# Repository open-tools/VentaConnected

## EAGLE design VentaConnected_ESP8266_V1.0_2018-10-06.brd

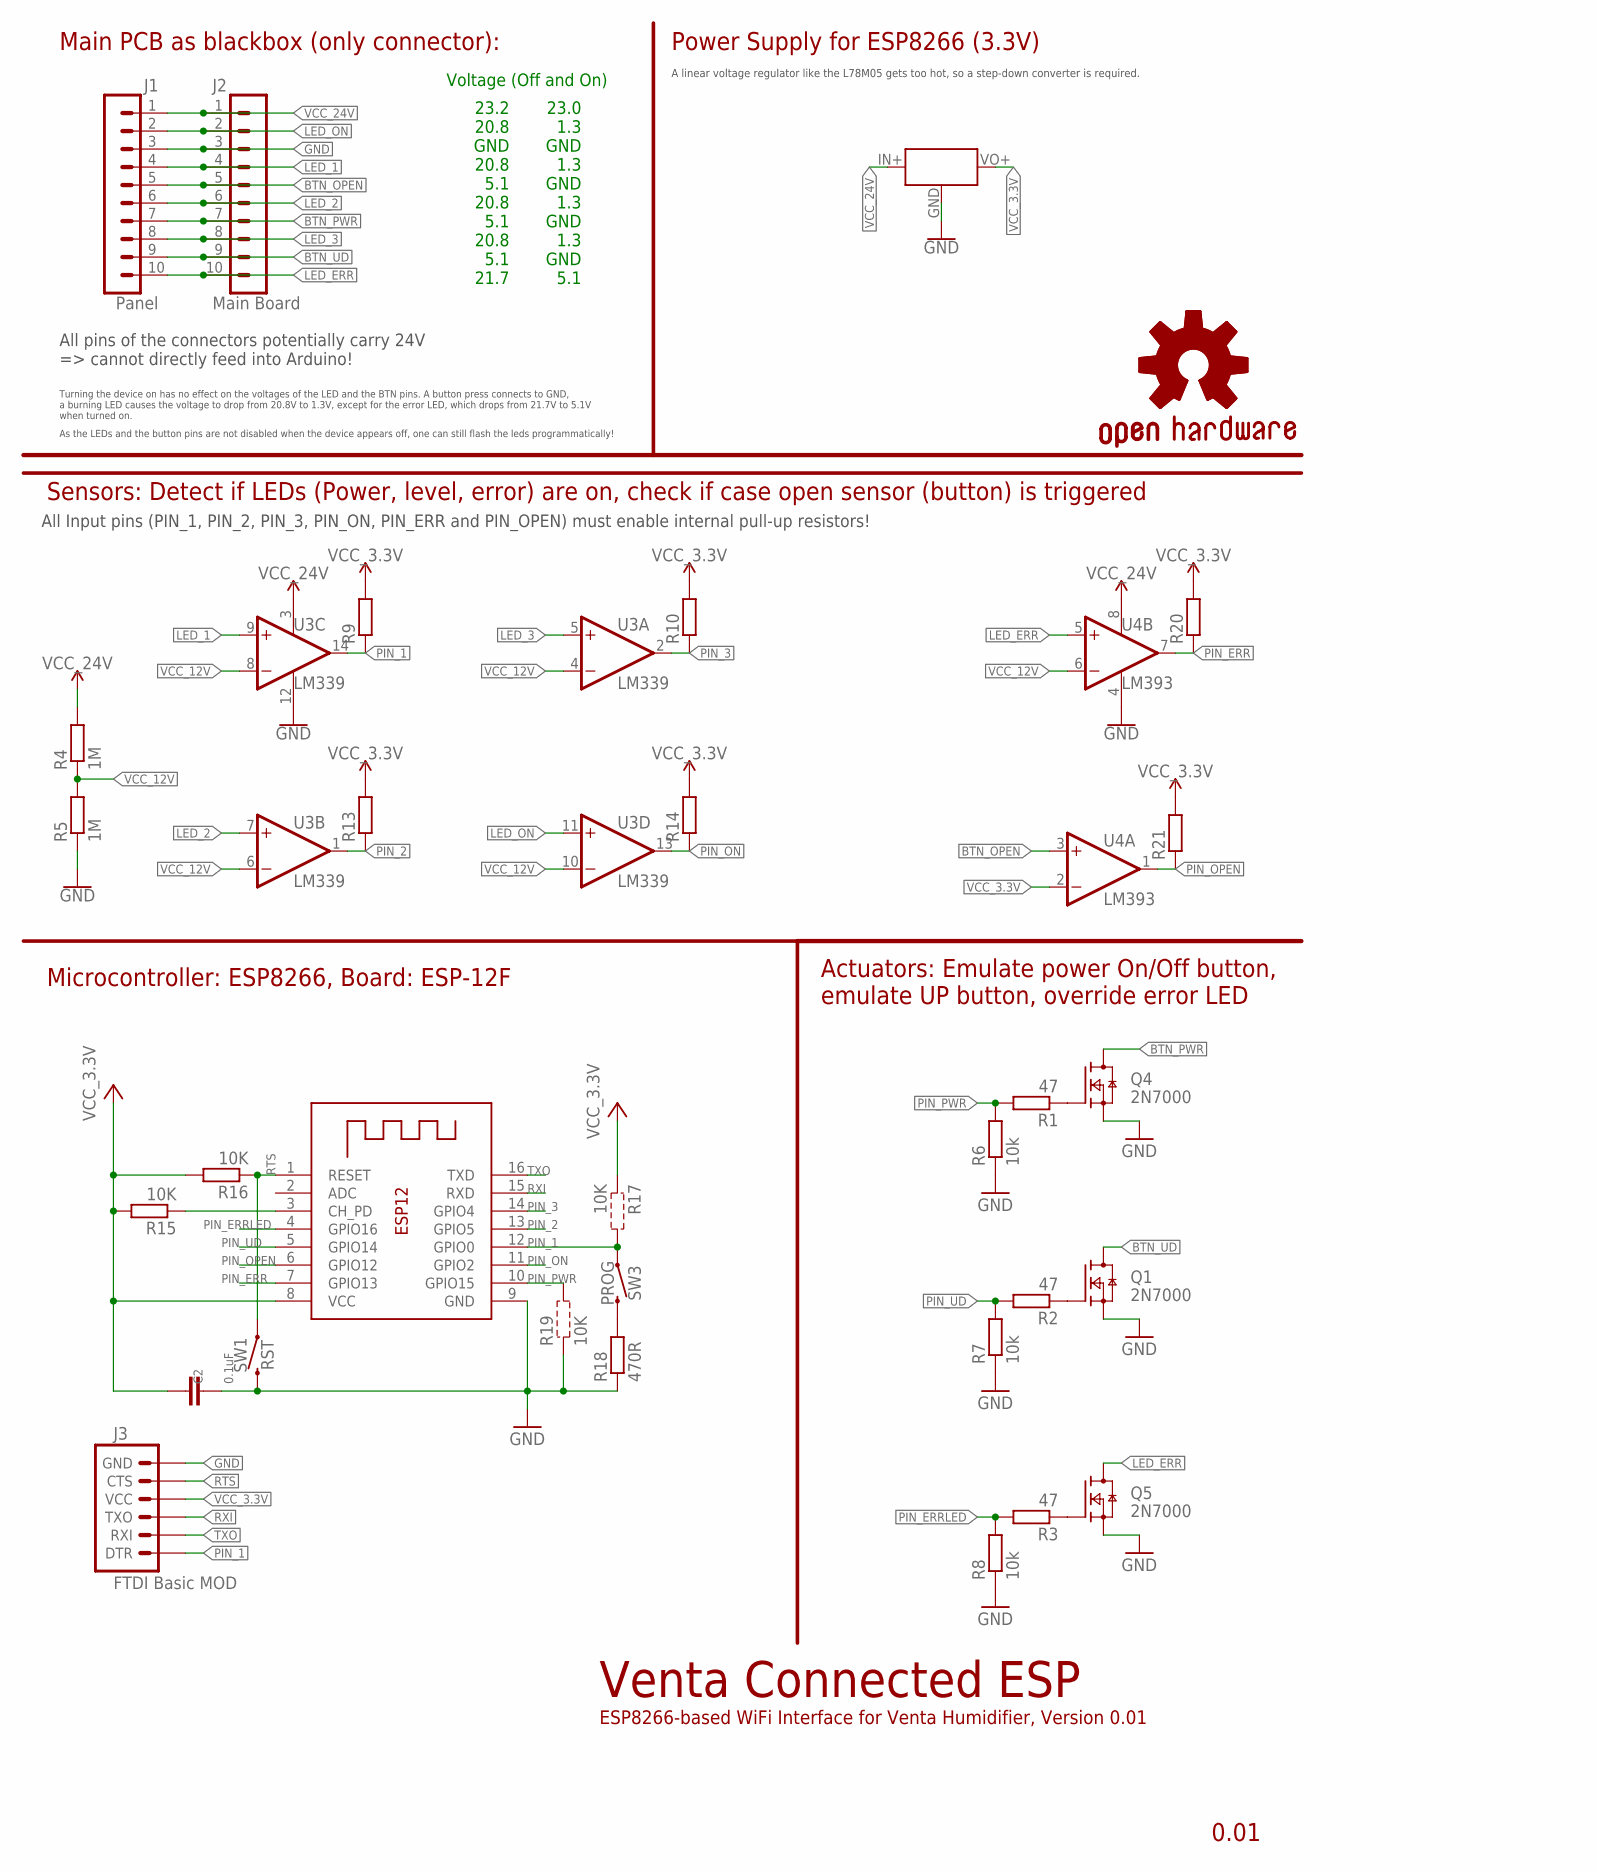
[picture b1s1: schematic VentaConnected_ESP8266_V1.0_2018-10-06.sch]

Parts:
C2: 0.1uF; C0805
GOLD_ORB_SM1: OSHWLOGO_GOLD_ORB_SM; OSHW2
J1: Panel; 2X5-SHROUDED
J2: Main Board; 2X5
J3: FTDI Basic MOD; 1X06
Q1, Q4, Q5: 2N7000; SOT23
R1, R2, R3: 47; R0805
R4, R5: 1M; R0805
R6, R7, R8: 10k; R0805
R9, R10, R13, R14, R20, R21: R-EU_R0805; R0805
R15, R16: 10K; R0805
R18: 470R; R0805
SW1: RST; TACTILE_SWITCH_SMD_6.0X3.5MM
SW3: PROG; TACTILE_SWITCH_SMD_6.0X3.5MM
U2: 3.3V_BUCK_CONVERTER; MINI_BUCK_CONVERTER_UPDOWN
U3: LM339; SO14
U4: LM393; SO08
X2: ESP-12e; ESP-12

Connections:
BTN_OPEN: J1.5, J2.5, U4.3 (+IN)
BTN_PWR: J1.7, J2.7, Q4.3 (D)
BTN_UD: J1.9, J2.9, Q1.3 (D)
CH_PD: R15.1, X2.3 (CH_PD)
GND: C2.1, J1.3, J2.3, J3.6 (GND), Q1.2 (S), Q4.2 (S), Q5.2 (S), R5.1, R6.1, R7.1, R8.1, R18.1, SW1.2, U2.GND, U3.12 (V-), U4.4 (V-), X2.9 (GND)
LED_1: J1.4, J2.4, U3.9 (+IN)
LED_2: J1.6, J2.6, U3.7 (+IN)
LED_3: J1.8, J2.8, U3.5 (+IN)
LED_ERR: J1.10, J2.10, Q5.3 (D), U4.5 (+IN)
LED_ON: J1.2, J2.2, U3.11 (+IN)
unnamed: Q4.1 (G), R1.1
unnamed: R18.2, SW3.2
unnamed: Q5.1 (G), R3.1
unnamed: Q1.1 (G), R2.1
PIN_1: J3.1 (DTR), R9.1, SW3.1, U3.14 (OUT), X2.12 (GPIO0)
PIN_2: R13.1, U3.1 (OUT), X2.13 (GPIO5)
PIN_3: R10.1, U3.2 (OUT), X2.14 (GPIO4)
PIN_ERR: R20.1, U4.7 (OUT), X2.7 (GPIO13)
PIN_ERRLED: R3.2, R8.2, X2.4 (GPIO16)
PIN_ON: R14.1, U3.13 (OUT), X2.11 (GPIO2)
PIN_OPEN: R21.1, U4.1 (OUT), X2.6 (GPIO12)
PIN_PWR: R1.2, R6.2, X2.10 (GPIO15)
PIN_UD: R2.2, R7.2, X2.5 (GPIO14)
RTS: J3.5 (CTS), R16.1, SW1.1, X2.1 (RESET)
RXI: J3.3 (TXO), X2.15 (RXD)
TXO: J3.2 (RXI), X2.16 (TXD)
VCC_3.3V: C2.2, J3.4 (VCC), R9.2, R10.2, R13.2, R14.2, R15.2, R16.2, R20.2, R21.2, U2.VO+ (VOUT), U4.2 (-IN), X2.8 (VCC)
VCC_12V: R4.1, R5.2, U3.4 (-IN), U3.6 (-IN), U3.8 (-IN), U3.10 (-IN), U4.6 (-IN)
VCC_24V: J1.1, J2.1, R4.2, U2.IN+ (VIN), U3.3 (V+), U4.8 (V+)

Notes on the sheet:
Power Supply for ESP8266 (3.3V)
ESP8266-based WiFi Interface for Venta Humidifier, Version 0.01
Venta Connected ESP
Actuators: Emulate power On/Off button, emulate UP button, override error LED
Sensors: Detect if LEDs (Power, level, error) are on, check if case open sensor (button) is triggered
Microcontroller: ESP8266, Board: ESP-12F
Main PCB as blackbox (only connector):
All pins of the connectors potentially carry 24V => cannot directly feed into Arduino!
A linear voltage regulator like the L78M05 gets too hot, so a step-down converter is required.
Voltage (Off and On)
23.2 20.8 GND 20.8 5.1 20.8 5.1 20.8 5.1 21.7
23.0 1.3 GND 1.3 GND 1.3 GND 1.3 GND 5.1
Turning the device on has no effect on the voltages of the LED and the BTN pins. A button press connects to GND, a burning LED causes the voltage to drop from 20.8V to 1.3V, except for the error LED, which drops from 21.7V to 5.1V when turned on.
As the LEDs and the button pins are not disabled when the device appears off, one can still flash the leds programmatically!
All Input pins (PIN_1, PIN_2, PIN_3, PIN_ON, PIN_ERR and PIN_OPEN) must enable internal pull-up resistors!

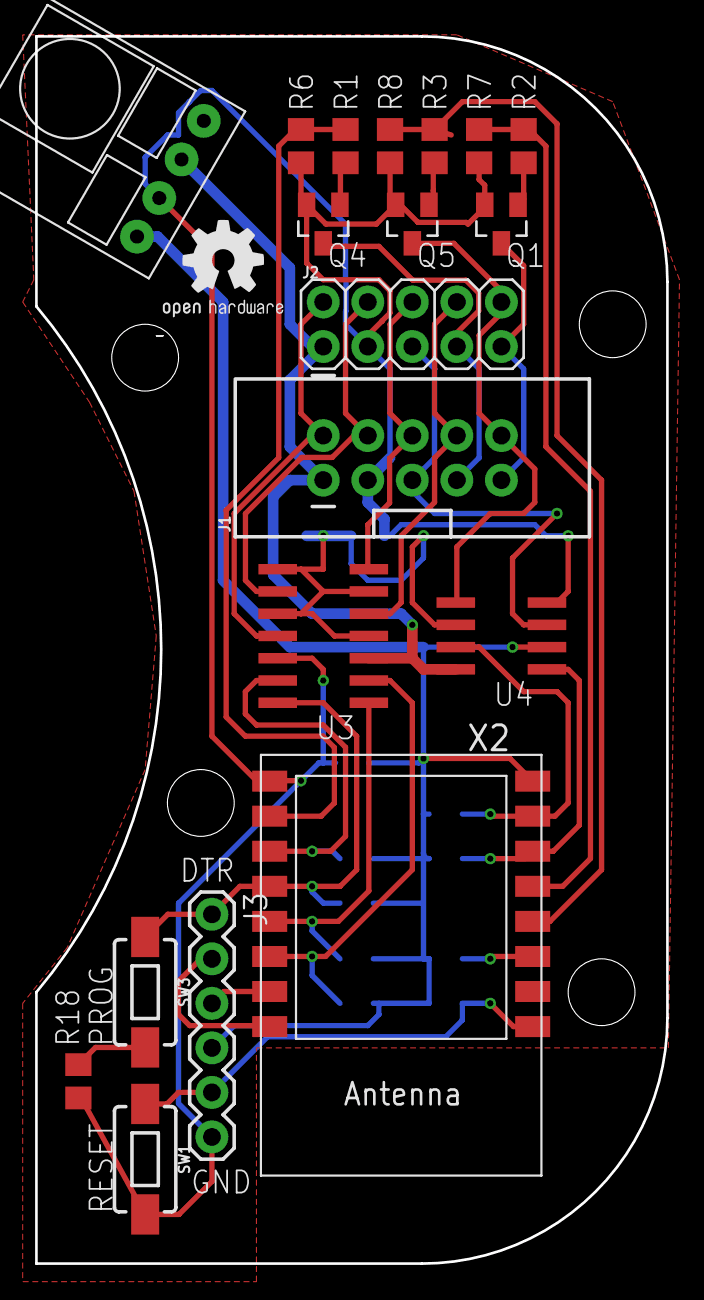
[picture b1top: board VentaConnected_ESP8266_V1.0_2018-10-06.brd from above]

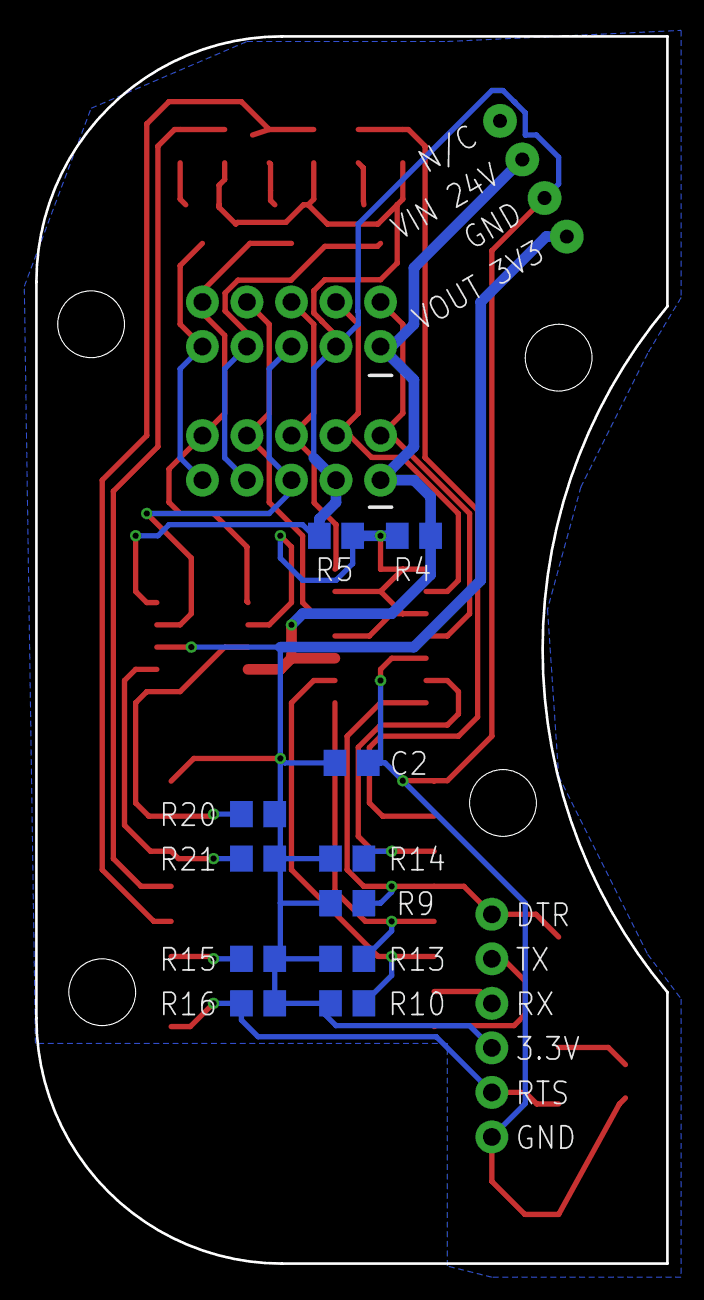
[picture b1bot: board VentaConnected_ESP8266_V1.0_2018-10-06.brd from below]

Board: 2 copper layers, 36.0 x 70.0 mm, 31 parts (11 on the bottom side), 29 nets.

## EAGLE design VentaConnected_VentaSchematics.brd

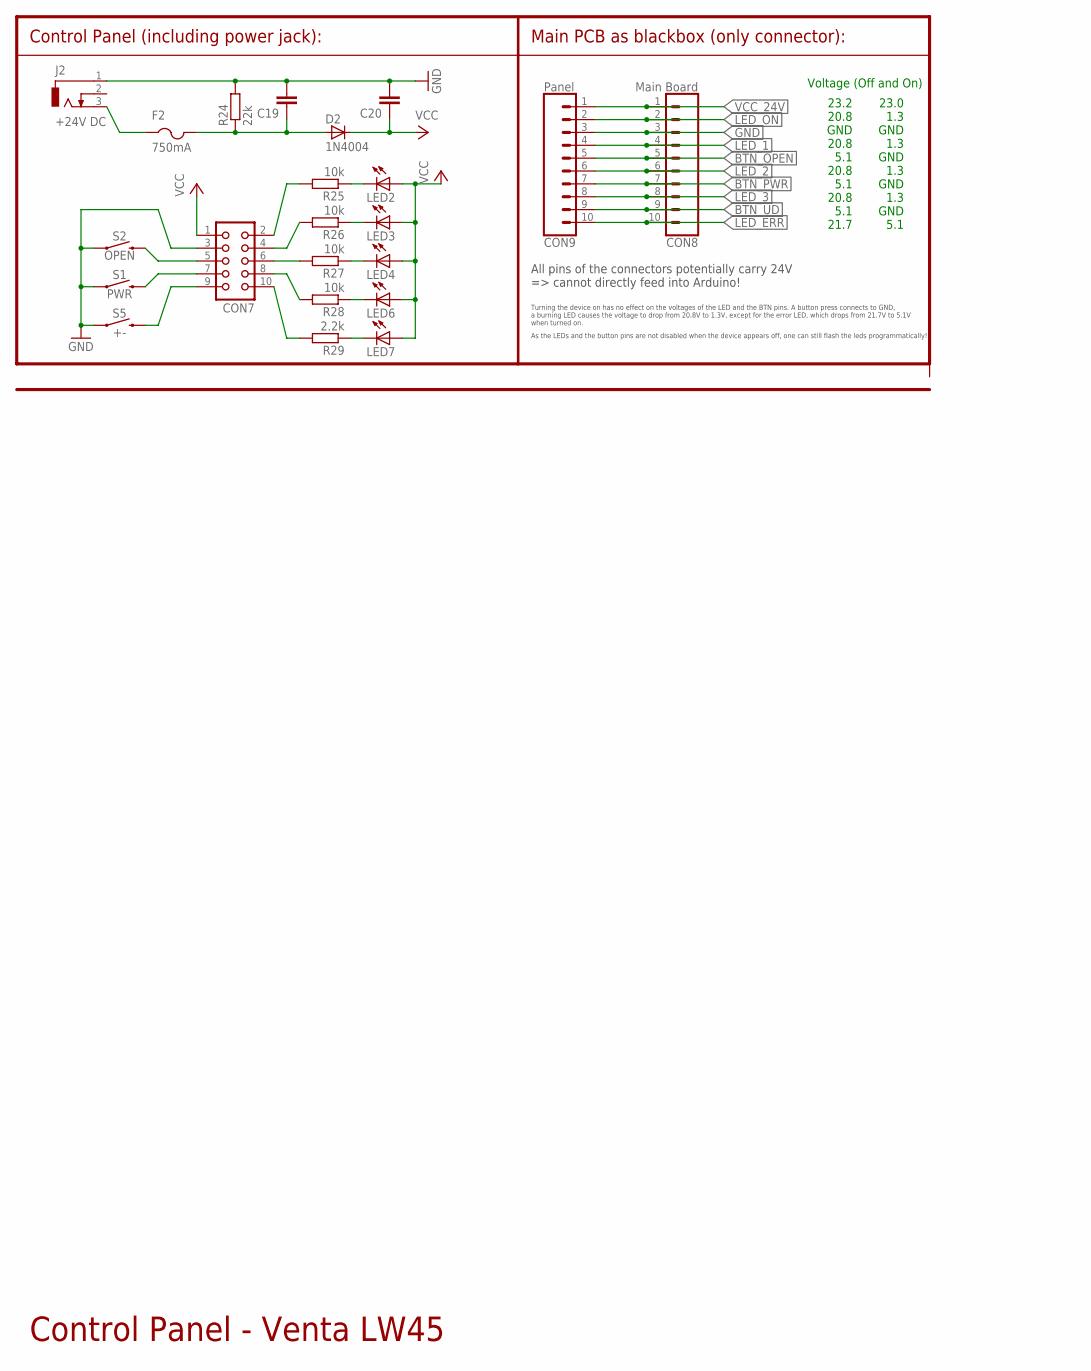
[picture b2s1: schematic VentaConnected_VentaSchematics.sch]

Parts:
C19, C20: C-EUC0805K; C0805K
CON7: CON10
CON8: Main Board; 1X10_LOCK_LONGPADS
CON9: Panel; 1X10_LOCK_LONGPADS
D2: 1N4004; MELF-MLL41
F2: 750mA; 1812
J2: +24V DC; DCJ0202
LED2, LED3, LED4, LED6, LED7: LEDCHIPLED_0805; CHIPLED_0805
R24: 22k; R0805
R25, R26, R27, R28: 10k; R0805
R29: 2.2k; R0805
S1: PWR; TACTILE_SWITCH_PTH_6.0MM
S2: OPEN; TACTILE_SWITCH_PTH_6.0MM
S5: +-; TACTILE_SWITCH_PTH_6.0MM

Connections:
BTN_OPEN: CON7.5, CON8.5, CON9.5, S2.3 (2)
BTN_PWR: CON7.7, CON8.7, CON9.7, S1.3 (2)
BTN_UD: CON7.9, CON8.9, CON9.9, S5.3 (2)
GND: C19.2, C20.2, CON7.3, CON8.3, CON9.3, J2.1, R24.2, S1.1, S2.1, S5.1
LED_1: CON7.4, CON8.4, CON9.4, R26.2
LED_2: CON7.6, CON8.6, CON9.6, R27.2
LED_3: CON7.8, CON8.8, CON9.8, R28.2
LED_ERR: CON7.10, CON8.10, CON9.10, R29.2
LED_ON: CON7.2, CON8.2, CON9.2, R25.2
unnamed: F2.1, J2.3
unnamed: C19.1, D2.2 (A), F2.2, R24.1
unnamed: LED2.C, R25.1
unnamed: LED7.C, R29.1
unnamed: LED3.C, R26.1
unnamed: LED4.C, R27.1
unnamed: LED6.C, R28.1
VCC: C20.1, D2.1 (C), LED2.A, LED3.A, LED4.A, LED6.A, LED7.A
VCC_24V: CON7.1, CON8.1, CON9.1

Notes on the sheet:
Control Panel - Venta LW45
Control Panel (including power jack):
Main PCB as blackbox (only connector):
All pins of the connectors potentially carry 24V => cannot directly feed into Arduino!
Voltage (Off and On)
23.2 20.8 GND 20.8 5.1 20.8 5.1 20.8 5.1 21.7
23.0 1.3 GND 1.3 GND 1.3 GND 1.3 GND 5.1
Turning the device on has no effect on the voltages of the LED and the BTN pins. A button press connects to GND, a burning LED causes the voltage to drop from 20.8V to 1.3V, except for the error LED, which drops from 21.7V to 5.1V when turned on.
As the LEDs and the button pins are not disabled when the device appears off, one can still flash the leds programmatically!

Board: 2 copper layers, 22 parts (0 on the bottom side), 18 nets, no tracks yet.

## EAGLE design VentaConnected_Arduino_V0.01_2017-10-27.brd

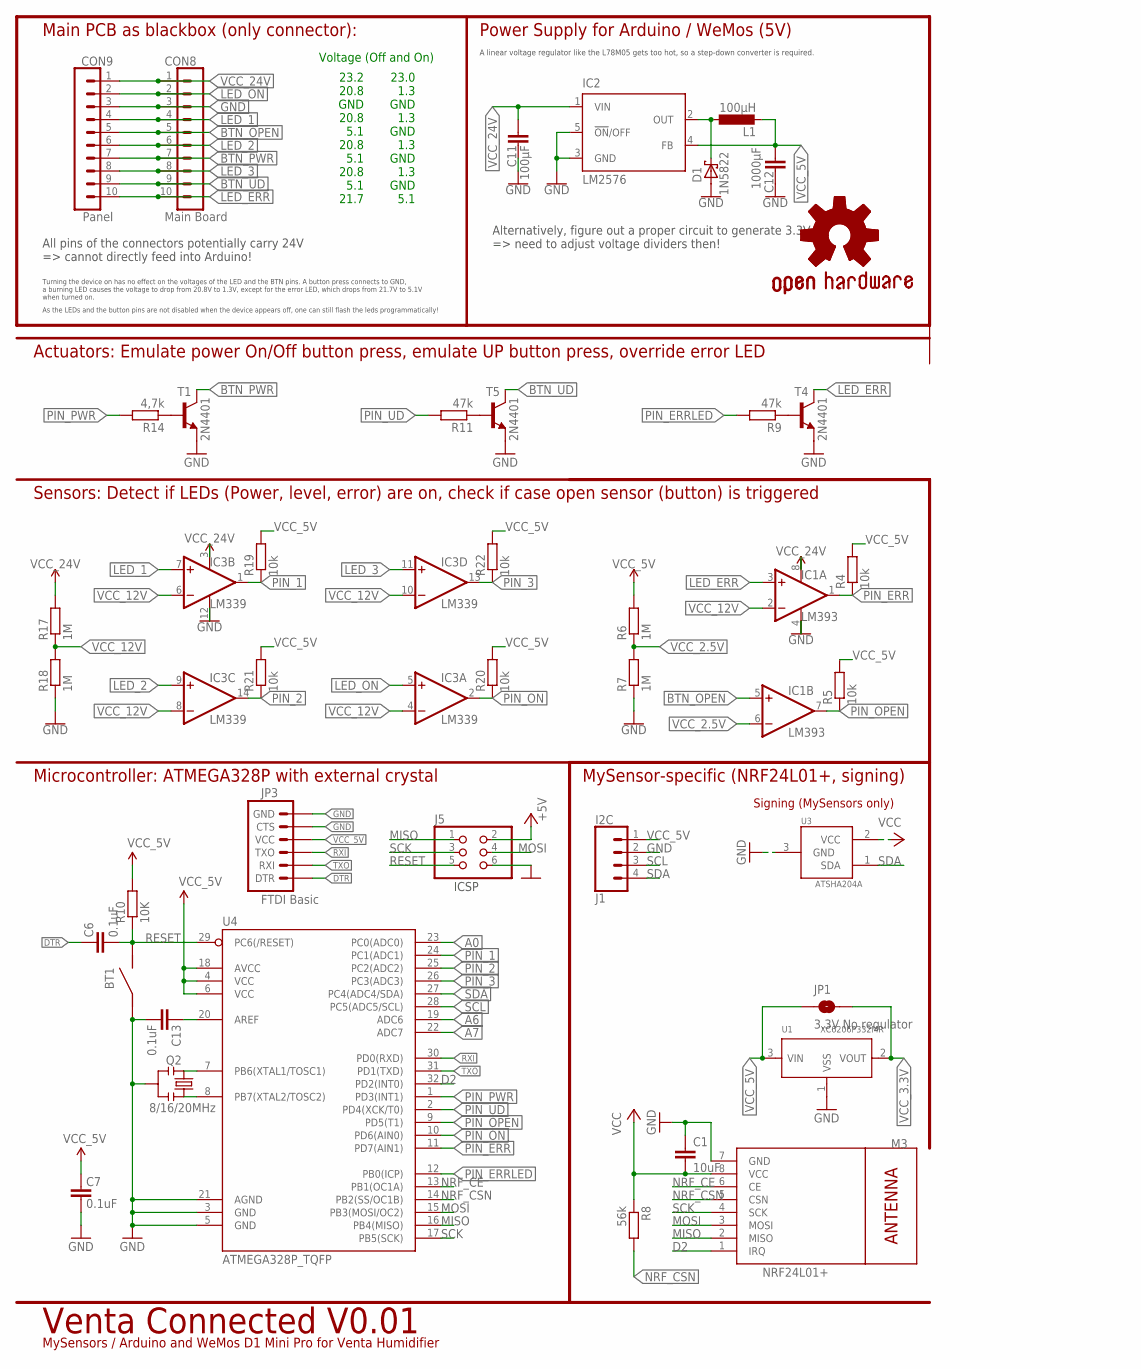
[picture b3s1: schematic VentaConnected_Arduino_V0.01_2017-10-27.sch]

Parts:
BT1: SWITCHPROMINI_RESET; SWITCH_SMD_PROMINI_RESET
C1: 10uF; C0805
C6, C7, C13: 0.1uF; 0603-CAP
C11: 100µF; C0805
C12: 1000µF; C0805
CON8: Main Board; 2X5
CON9: Panel; 2X5-SHROUDED
D1: 1N5822; SMB
GOLD_ORB_SM1: OSHWLOGO_GOLD_ORB_SM; OSHW2
IC1: LM393; SO08
IC2: LM2576; TO263-5
IC3: LM339; SO14
J1: I2C; 1X04
J5: PINHD-2X3; 2X03
JP1: 3.3V No regulator; SMT-JUMPER_2_NO_SILK
JP3: FTDI Basic; 1X06
L1: 100µH; POWER-CHOKE_WE-TPC
M3: NRF24L01+; WIRELESS-NRF24L01-SMD
Q2: 8/16/20MHz; RESONATOR-SMD-1:1
R4, R5, R19, R20, R21, R22: 10k; R0805
R6, R7, R17, R18: 1M; R0805
R8: 56k; R0805
R9, R11: 47k; R0805
R10: 10K; R0805
R14: 4,7k; R0805
T1, T4, T5: 2N4401; SOT23-BEC
U1: XC6206P332MR; SOT-23
U3: ATSHA204A; SOT23-3
U4: ATMEGA328P_TQFP; TQFP32-08

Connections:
A0: U4.23 (PC0(ADC0))
A6: U4.19 (ADC6)
A7: U4.22 (ADC7)
AREF: C13.2, U4.20 (AREF)
BTN_OPEN: CON8.5, CON9.5, IC1.5 (+IN)
BTN_PWR: CON8.7, CON9.7, T1.C
BTN_UD: CON8.9, CON9.9, T5.C
D2: M3.1 (IRQ), U4.32 (PD2(INT0))
DTR: C6.2, JP3.1 (DTR)
GND: BT1.IN, C7.1, C11.2, C12.2, C13.1, CON8.3, CON9.3, D1.A, IC1.4 (V-), IC2.3 (GND), IC2.5 (!ON!/OFF), IC3.12 (V-), J1.2, J5.6, JP3.5 (CTS), JP3.6 (GND), Q2.2, R7.1, R18.1, T1.E, T4.E, T5.E, U4.3 (GND), U4.5 (GND), U4.21 (AGND)
GND_ARD: C1.1, M3.7 (GND), U3.3 (GND)
LED_1: CON8.4, CON9.4, IC3.7 (+IN)
LED_2: CON8.6, CON9.6, IC3.9 (+IN)
LED_3: CON8.8, CON9.8, IC3.11 (+IN)
LED_ERR: CON8.10, CON9.10, IC1.3 (+IN), T4.C
LED_ON: CON8.2, CON9.2, IC3.5 (+IN)
MISO: J5.1, M3.2 (MISO), U4.16 (PB4(MISO))
MOSI: J5.4, M3.3 (MOSI), U4.15 (PB3(MOSI/OC2))
unnamed: D1.C, IC2.2 (OUT), L1.1
unnamed: R14.1, T1.B
unnamed: R9.1, T4.B
unnamed: R11.1, T5.B
unnamed: Q2.3, U4.8 (PB7(XTAL2/TOSC2))
unnamed: Q2.1, U4.7 (PB6(XTAL1/TOSC1))
NRF_CE: M3.6 (CE), U4.13 (PB1(OC1A))
NRF_CSN: M3.5 (CSN), R8.2, U4.14 (PB2(SS/OC1B))
PIN_1: IC3.1 (OUT), R19.1, U4.24 (PC1(ADC1))
PIN_2: IC3.14 (OUT), R21.1, U4.25 (PC2(ADC2))
PIN_3: IC3.13 (OUT), R22.1, U4.26 (PC3(ADC3))
PIN_ERR: IC1.1 (OUT), R4.1, U4.11 (PD7(AIN1))
PIN_ERRLED: R9.2, U4.12 (PB0(ICP))
PIN_ON: IC3.2 (OUT), R20.1, U4.10 (PD6(AIN0))
PIN_OPEN: IC1.7 (OUT), R5.1, U4.9 (PD5(T1))
PIN_PWR: R14.2, U4.1 (PD3(INT1))
PIN_UD: R11.2, U4.2 (PD4(XCK/T0))
RESET: BT1.OUT, C6.1, J5.5, R10.1, U4.29 (PC6(/RESET))
RXI: JP3.3 (TXO), U4.30 (PD0(RXD))
SCK: J5.3, M3.4 (SCK), U4.17 (PB5(SCK))
SCL: J1.3, U4.28 (PC5(ADC5/SCL))
SDA: J1.4, U3.1 (SDA), U4.27 (PC4(ADC4/SDA))
TXO: JP3.2 (RXI), U4.31 (PD1(TXD))
VCC_2.5V: IC1.6 (-IN), R6.1, R7.2
VCC_3.3V: C1.2, JP1.2, M3.8 (VCC), R8.1, U1.2 (VOUT)
VCC_5V: C7.2, C12.1, IC2.4 (FB), J1.1, J5.2, JP1.1, JP3.4 (VCC), L1.2, R4.2, R5.2, R6.2, R10.2, R19.2, R20.2, R21.2, R22.2, U1.3 (VIN), U3.2 (VCC), U4.4 (VCC), U4.6 (VCC), U4.18 (AVCC)
VCC_12V: IC1.2 (-IN), IC3.4 (-IN), IC3.6 (-IN), IC3.8 (-IN), IC3.10 (-IN), R17.1, R18.2
VCC_24V: C11.1, CON8.1, CON9.1, IC1.8 (V+), IC2.1 (VIN), IC3.3 (V+), R17.2
VSS: U1.1 (VSS)

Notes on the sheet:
Signing (MySensors only)
MySensor-specific (NRF24L01+, signing)
Power Supply for Arduino / WeMos (5V)
MySensors / Arduino and WeMos D1 Mini Pro for Venta Humidifier
Venta Connected V0.01
Actuators: Emulate power On/Off button press, emulate UP button press, override error LED
Sensors: Detect if LEDs (Power, level, error) are on, check if case open sensor (button) is triggered
Microcontroller: ATMEGA328P with external crystal
Alternatively, figure out a proper circuit to generate 3.3V => need to adjust voltage dividers then!
Main PCB as blackbox (only connector):
All pins of the connectors potentially carry 24V => cannot directly feed into Arduino!
A linear voltage regulator like the L78M05 gets too hot, so a step-down converter is required.
Voltage (Off and On)
23.2 20.8 GND 20.8 5.1 20.8 5.1 20.8 5.1 21.7
23.0 1.3 GND 1.3 GND 1.3 GND 1.3 GND 5.1
Turning the device on has no effect on the voltages of the LED and the BTN pins. A button press connects to GND, a burning LED causes the voltage to drop from 20.8V to 1.3V, except for the error LED, which drops from 21.7V to 5.1V when turned on.
As the LEDs and the button pins are not disabled when the device appears off, one can still flash the leds programmatically!
ICSP

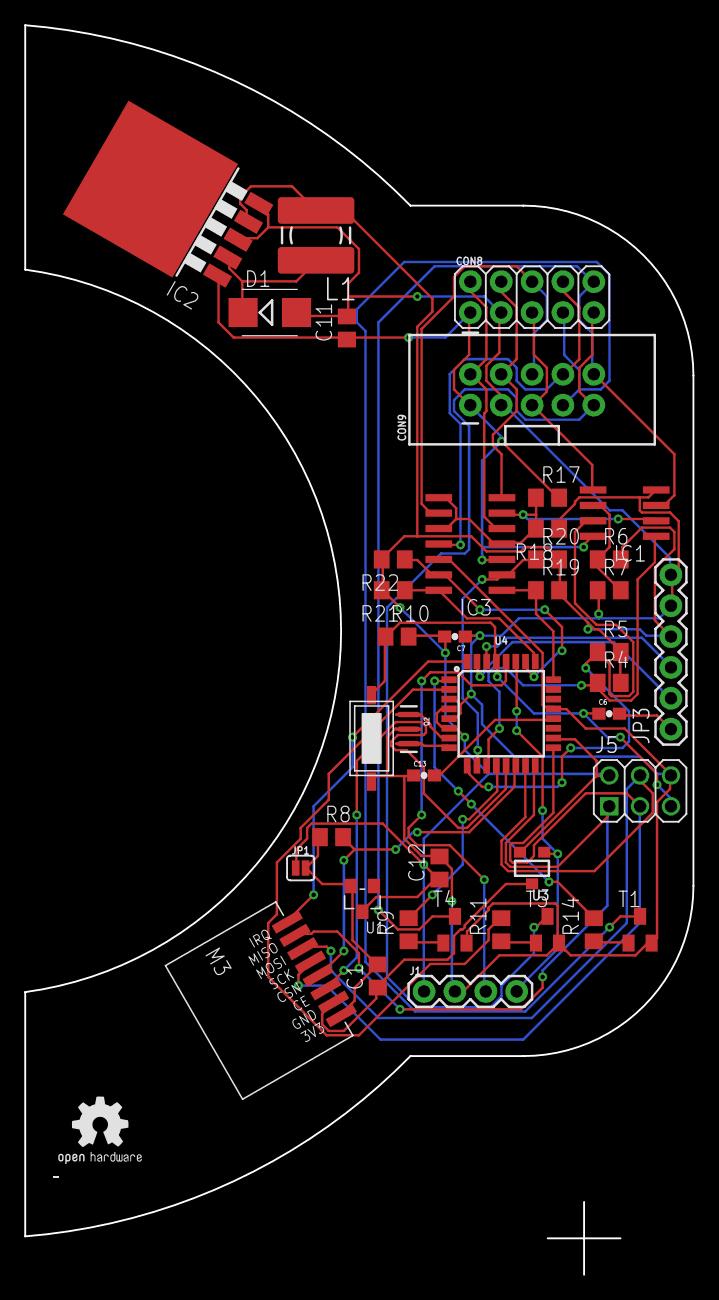
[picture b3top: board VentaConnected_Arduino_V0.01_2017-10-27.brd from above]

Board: 2 copper layers, 55.0 x 102.8 mm, 42 parts (0 on the bottom side), 43 nets.

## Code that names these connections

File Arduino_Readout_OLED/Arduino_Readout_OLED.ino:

/*********************************************************************
This is an example for our Monochrome OLEDs based on SSD1306 drivers

  Pick one up today in the adafruit shop!
  ------> http://www.adafruit.com/category/63_98

This example is for a 128x64 size display using I2C to communicate
3 pins are required to interface (2 I2C and one reset)

Adafruit invests time and resources providing this open source code, 
please support Adafruit and open-source hardware by purchasing 
products from Adafruit!

Written by Limor Fried/Ladyada  for Adafruit Industries.  
BSD license, check license.txt for more information
All text above, and the splash screen must be included in any redistribution
*********************************************************************/
//#define SSD1306_128_64

//#include <SPI.h>
//#include <Wire.h>
//#include <Adafruit_GFX.h>
//#include <Adafruit_SSD1306.h>

//#define OLED_RESET 4
//Adafruit_SSD1306 display(OLED_RESET);
//#if (SSD1306_LCDHEIGHT != 64)
//# error(F("Height incorrect, please fix Adafruit_SSD1306.h!"));
//#endif

#include <SSD1306Ascii.h>
#include <SSD1306AsciiAvrI2c.h>
// 0X3C+SA0 - 0x3C or 0x3D
#define I2C_ADDRESS 0x3C
SSD1306AsciiAvrI2c oled;

#define PIN_PWR  3
#define PIN_UD   4
#define PIN_OPEN 5
#define LED_ON   6
#define LED_1    A1
#define LED_2    A2
#define LED_3    A3
#define LED_ERR  7
#define PIN_ERR  8


void setup()   {                
  Serial.begin(9600);

  // by default, we'll generate the high voltage from the 3.3v line internally! (neat!)
//  display.begin(SSD1306_SWITCHCAPVCC, 0x3D);  // initialize with the I2C addr 0x3D (for the 128x64)
//  display.begin(SSD1306_SWITCHCAPVCC, 0x3C);  // initialize with the I2C addr 0x3D (for the 128x64)
  // init done
//  display.clearDisplay();
  oled.begin(&Adafruit128x64, I2C_ADDRESS);
  oled.setFont(Adafruit5x7);

  // Set up pins:
  // Button & LED Actions (output):
  //   - PIN_PWR  D3 ... Power button press
  //   - PIN_UD   D4 ... Up/Down button press
  //   - PIN_ERR  D8 ... Control Error LED
  // Button detection (input, pullup!):
  //   - PIN_OPEN D5 ... Case open Button => causes Error
  // LED detection (input, NO pullup, already connected to +VCC via LED+resistor):
  //   - LED_ON   D6 ... Power LED 
  //   - LED_ERR  D7 ... Error LED
  //   - LED_1    A1 ... Level 1 LED
  //   - LED_2    A2 ... Level 2 LED
  //   - LED_3    A3 ... Level 3 LED

  pinMode(PIN_PWR, OUTPUT);
  pinMode(PIN_UD,  OUTPUT);
  pinMode(PIN_OPEN,INPUT_PULLUP);
  pinMode(LED_ON,  INPUT);
  pinMode(LED_1,   INPUT);
  pinMode(LED_2,   INPUT);
  pinMode(LED_3,   INPUT);
  pinMode(LED_ERR, INPUT);
  pinMode(PIN_ERR, OUTPUT);
  digitalWrite(PIN_ERR, HIGH);

  pinMode(A0, INPUT_PULLUP);
}

int level = 0;
bool power = false;
bool error = false;
bool caseopen = false;

void loop() {
  power = digitalRead(LED_ON) == LOW;
  error = digitalRead(LED_ERR) == LOW;
  caseopen = digitalRead(PIN_OPEN) == LOW;

  if (digitalRead(LED_1) == LOW) {
    level = 1;
  }
  if (digitalRead(LED_2) == LOW) {
    level = 2;
  }
  if (digitalRead(LED_3) == LOW) {
    level = 3;
  }

int pwr = digitalRead(A0);
//digitalWrite(PIN_PWR, digitalRead(A0));
//  digitalRead(A6)
//  digitalRead(A7)


  oled.clear();
  oled.set2X();
  oled.print(F("Power: "));
  oled.println(power ? F("ON") : F("OFF"));

  oled.print(F("Error: "));
  oled.println(error ? F("YES") : F("no"));

  oled.set1X();
  oled.print(F("Case Open: "));
  oled.println(caseopen ? F("YES") : F("no"));

  oled.set2X();
  oled.print(F("Level "));
  oled.println(level);

  oled.set1X();
  oled.print(F("pwr:"));oled.print(pwr); oled.print(F(", "));
  oled.println();


//  ledOn(PIN_ERR);
//  delay(150);
//  ledOff(PIN_ERR);
//  delay(350);

  pressButton(PIN_UD);
  delay(1000);

}

void pressButton(int pin) {
  digitalWrite(pin, HIGH);
  delay(100);
  digitalWrite(pin, LOW);
}
void ledOn(int pin) {
  digitalWrite(pin, LOW);
}
void ledOff(int pin) {
  digitalWrite(pin, HIGH);
}

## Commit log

2017-10-30 Initial commit, breadboard circuit is working (with MySensors), PCB design missing
2017-12-09 First PCB versions finished, breadboard prototype with arduino fully running
2018-10-14 V1.0: ESP-Version finished
2018-10-14 Add BOM
2018-10-14 Add CERN OHL 1.2 license documents

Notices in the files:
parts and their libraries:
SparkFun-Jumpers: Licensing: Creative Commons ShareAlike 4.0 International - https://creativecommons.org/licenses/by-sa/4.0
NXP_60_26022015: This library may be distributed and adapted freely for any purpose, as long as NXP is credited and any new creation is licensed under the same terms.
